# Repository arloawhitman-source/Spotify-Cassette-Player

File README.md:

# What Is Spotify Cassette Player?
I am making a spotify display which will show album covers, lyrics, and have audio control functionality. This is placed into a 3d printed case made to look like a cassette player. The project uses a small quad color e-ink display to display the information.

# Features
This project uses a small microcontroller especially made for e-ink displays, this is paired with a adafruit AirLift to make it work completely on its own. It also has a programable button for future expansion or ideas. It features three buttons for music control to be implemented which will happen after I ensure that the rest of the code works.

# Assembly

# Case

# Wiring Diagram/PCB

# Code
The code in this project is largely untested however this page will be updated with final code once I can test it. One of the biggest problems with using the RP2040 is that it has very little on board ram or memory, to download and scale down images I wrote a script to be hosted on pythonanywhere to communicate with your project. Again I will update this page with further instructions once I am able to test the communication between my project and the pythonanywhere site.

# Spotify For Developers
In order for this project to work you must first set up a spotify developer project. This is done by going to spotify for developers website and logging in to spotify like normal, next create a project and give it an appropriate name and description. Finally under the call backs add these two links: https://YOURUSERNAMEHERE.pythonanywhere.com/callback http://127.0.0.1:8080/callback Last save your project and ensure the callback links match the ones running on your project.

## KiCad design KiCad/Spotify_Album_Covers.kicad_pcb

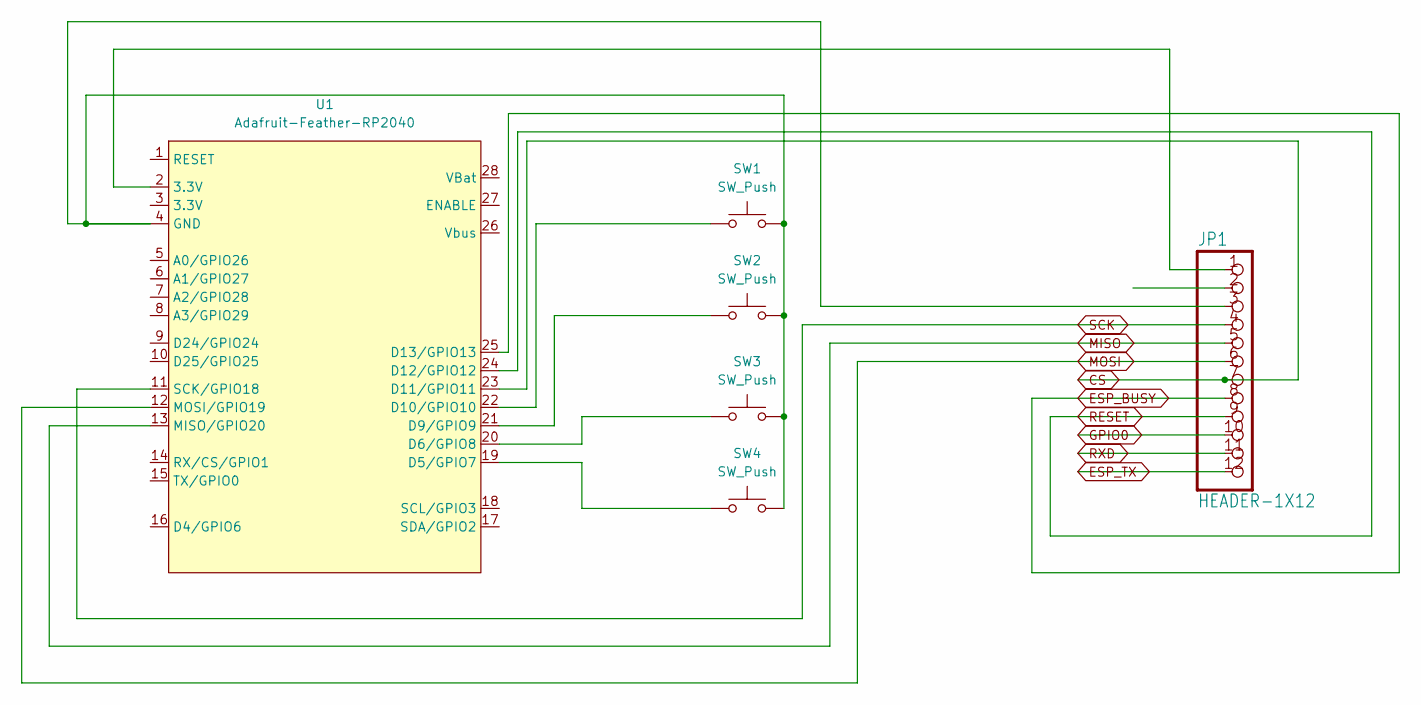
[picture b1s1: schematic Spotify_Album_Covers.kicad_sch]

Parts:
JP1: HEADER-1X12; PinHeader_1x12_P2.54mm_Vertical
SW1, SW2, SW3, SW4: SW_Push; SW_Tactile_SKHH_Angled
U1: Adafruit-Feather-RP2040

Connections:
CS: JP1.7, U1.23 (D11/GPIO11)
ESP_BUSY: JP1.8, U1.25 (D13/GPIO13)
ESP_TX: JP1.12
GPIO0: JP1.10
MISO: JP1.5, U1.13 (MISO/GPIO20)
MOSI: JP1.6, U1.12 (MOSI/GPIO19)
unnamed: JP1.1, U1.2 (3.3V)
unnamed: SW4.1, U1.19 (D5/GPIO7)
unnamed: SW3.1, U1.20 (D6/GPIO8)
unnamed: SW2.1, U1.21 (D9/GPIO9)
unnamed: SW1.1, U1.22 (D10/GPIO10)
unnamed: JP1.3, SW1.2, SW2.2, SW3.2, SW4.2, U1.4 (GND)
RESET: JP1.9, U1.24 (D12/GPIO12)
RXD: JP1.11
SCK: JP1.4, U1.11 (SCK/GPIO18)

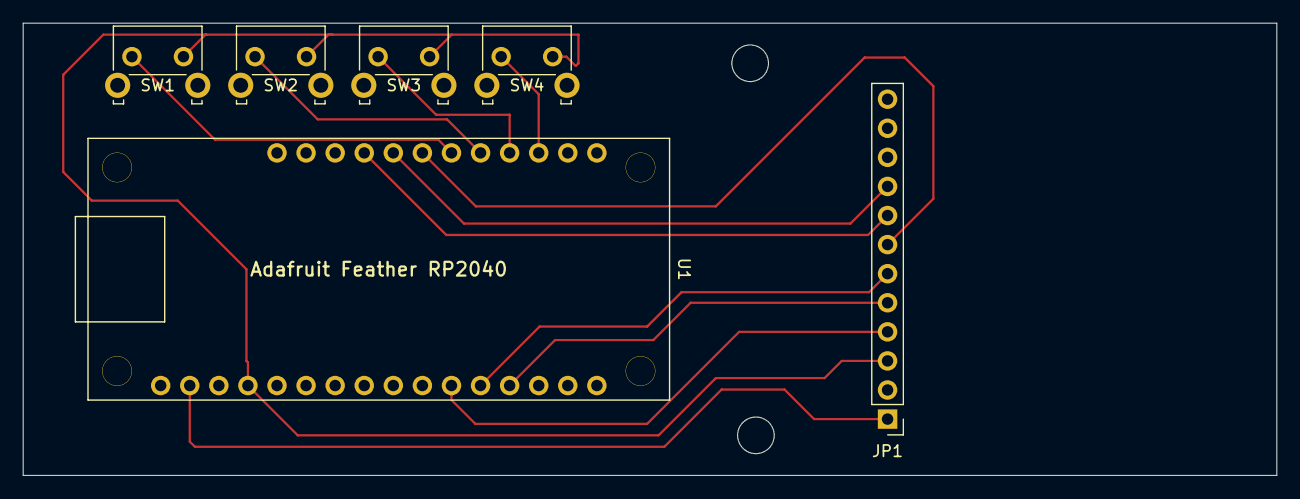
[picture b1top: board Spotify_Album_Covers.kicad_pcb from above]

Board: 2 copper layers, 109.5 x 39.5 mm, 6 parts (0 on the bottom side), 12 nets.
